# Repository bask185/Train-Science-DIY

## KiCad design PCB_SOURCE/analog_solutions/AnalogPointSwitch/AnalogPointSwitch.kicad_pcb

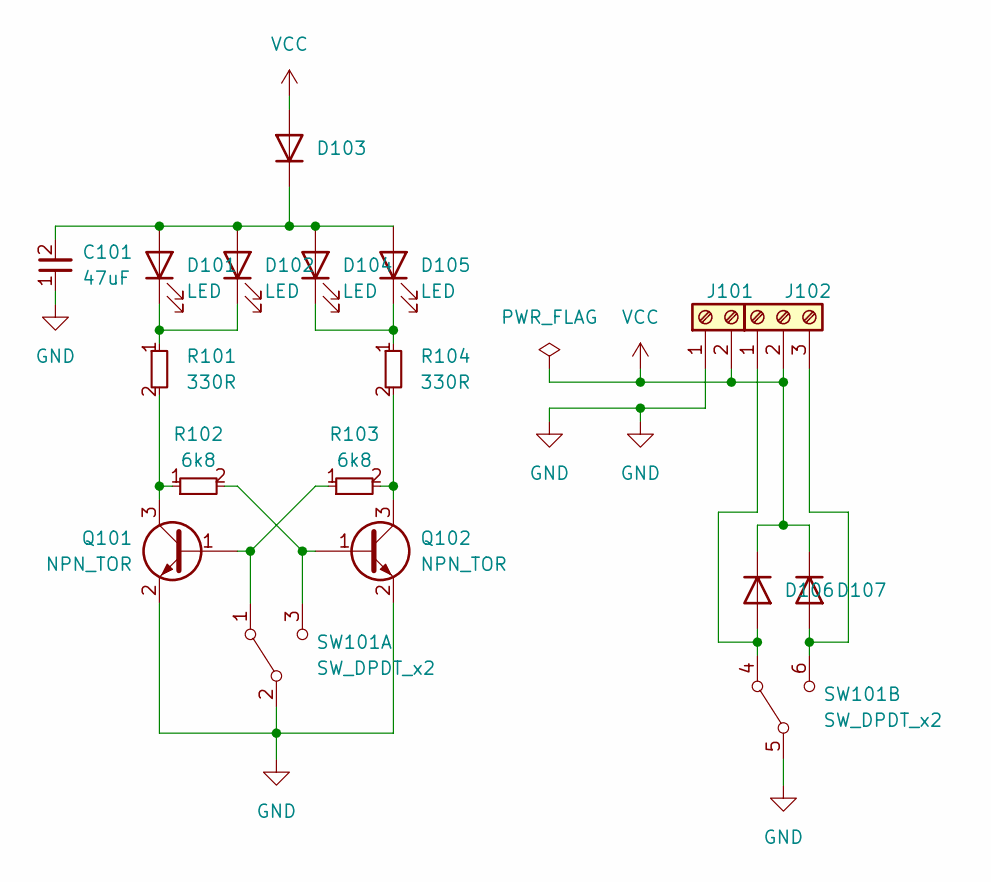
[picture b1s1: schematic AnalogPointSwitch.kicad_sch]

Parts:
C101: 47uF; C_1206_3216Metric; JLCPCB Part# C96123
D101, D102, D104, D105: LED; LED_D3.0mm
D103, D106, D107: 1N4148WS; D_SOD-323; JLCPCB Part# C2128
J101: Screw_Terminal_01x02; PhoenixContact_MCV_1,5_2-G-3.5_1x02_P3.50mm_Vertical
J102: Screw_Terminal_01x03; PhoenixContact_MCV_1,5_3-G-3.5_1x03_P3.50mm_Vertical
Q101, Q102: NPN_TOR; SOT-23; JLCPCB Part# C2145
R101, R104: 330R; R_0603_smalltext; JLCPCB Part# C23138
R102, R103: 6k8; R_0603_smalltext; JLCPCB Part# C23212
SW101: SW_DPDT_x2; MTS_DPDT

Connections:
GND: C101.1, J101.1, Q101.2 (E), Q102.2 (E), SW101.2 (B), SW101.5 (B)
unnamed: C101.2, D101.2 (A), D102.2 (A), D103.1 (K), D104.2 (A), D105.2 (A)
unnamed: D101.1 (K), D102.1 (K), R101.1
unnamed: D104.1 (K), D105.1 (K), R104.1
unnamed: D106.2 (A), J102.1, SW101.4 (A)
unnamed: D107.2 (A), J102.3, SW101.6 (C)
unnamed: Q101.1 (B), R103.1, SW101.1 (A)
unnamed: Q101.3 (C), R101.2, R102.1
unnamed: Q102.1 (B), R102.2, SW101.3 (C)
unnamed: Q102.3 (C), R103.2, R104.2
VCC: D103.2 (A), D106.1 (K), D107.1 (K), J101.2, J102.2

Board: 2 copper layers, 17 parts (5 on the bottom side), 11 nets, no tracks yet.

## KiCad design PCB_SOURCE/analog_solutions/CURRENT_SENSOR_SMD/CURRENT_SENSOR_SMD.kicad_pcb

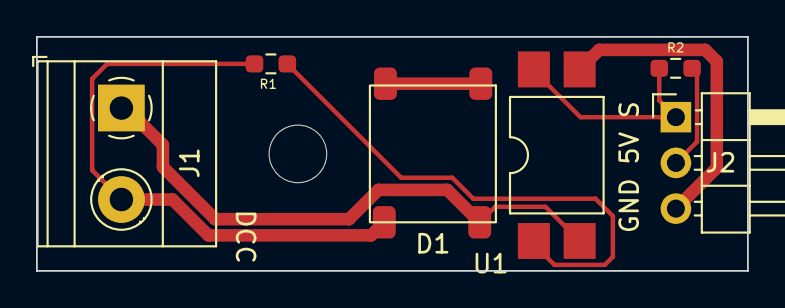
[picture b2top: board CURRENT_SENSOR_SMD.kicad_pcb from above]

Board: 2 copper layers, 39.5 x 13.0 mm, 6 parts (0 on the bottom side), 7 nets.

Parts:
D1: 4A rectifier
J1: Screw_Terminal_01x02; TerminalBlock_Phoenix_MKDS-1,5-2-5.08_1x02_P5.08mm_Horizont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
J2: Conn_01x03_Pin; PinHeader_1x03_P2.54mm_Horizontal
R1: 47R; R_0603_smalltext
R2: 10k; R_0603_smalltext
U1: EL814; SMDIP-4_W9.53mm

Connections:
+5V: J2.2, R2.2
GND: J2.3, U1.3
unnamed: D1.1 (+), D1.2 (-)
unnamed: D1.4, J1.1, U1.2
unnamed: D1.3, J1.2, R1.2
unnamed: J2.1, R2.1, U1.4
unnamed: R1.1, U1.1

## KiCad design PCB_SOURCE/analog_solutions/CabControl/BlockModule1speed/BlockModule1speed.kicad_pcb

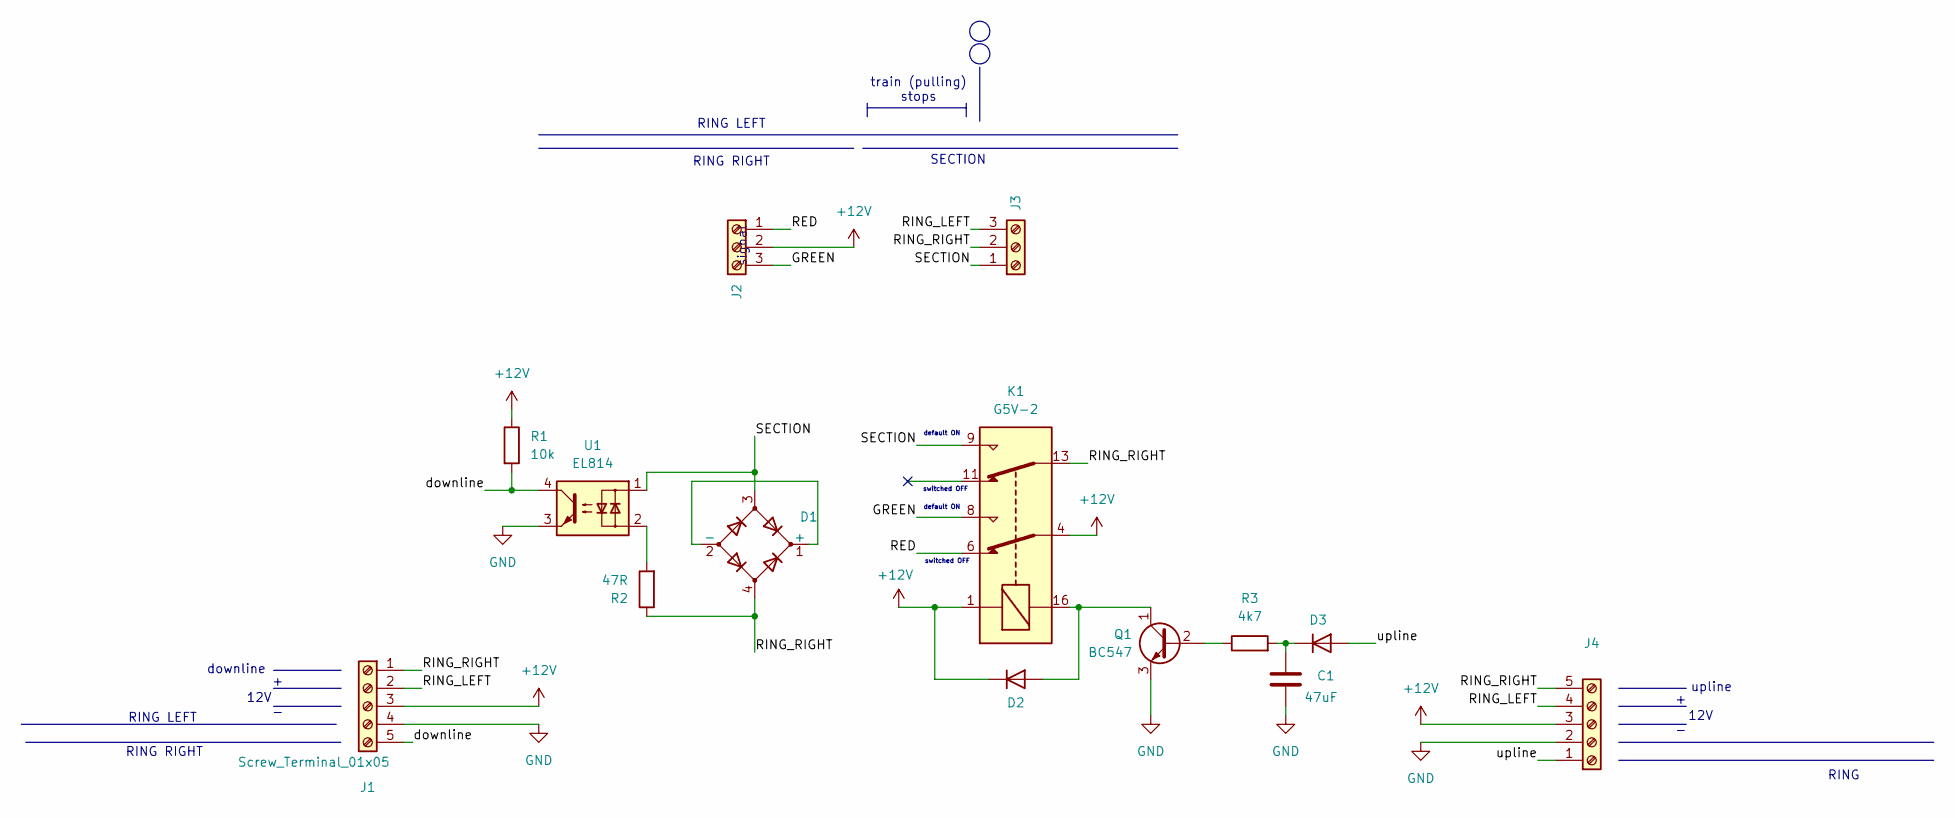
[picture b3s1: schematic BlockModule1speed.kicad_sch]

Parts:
C1: 47uF; C_Disc_D3.0mm_W2.0mm_P2.50mm
D1: D_Bridge_+-AA; Diode_Bridge_Round_D9.0mm
D2, D3: D; D_DO-34_SOD68_P7.62mm_Horizontal
J1, J4: Screw_Terminal_01x05; PhoenixContact_MC_1,5_5-G-3.5_1x05_P3.50mm_Horizontal
J2, J3: Screw_Terminal_01x03; PhoenixContact_MC_1,5_3-G-3.5_1x03_P3.50mm_Horizontal
K1: G5V-2; Relay_DPDT_Omron_G5V-2
Q1: BC547; TO-92_Inline_Wide
R1: 10k; R_Axial_DIN0204_L3.6mm_D1.6mm_P7.62mm_Horizontal
R2: 47R; R_Axial_DIN0204_L3.6mm_D1.6mm_P7.62mm_Horizontal
R3: 4k7; R_Axial_DIN0204_L3.6mm_D1.6mm_P7.62mm_Horizontal
U1: EL814; DIP-4_W7.62mm

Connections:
+12V: D2.1 (K), J1.3, J2.2, J4.3, K1.1, K1.4, R1.1
/GREEN: J2.3, K1.8
/RED: J2.1, K1.6
/RING_LEFT: J1.2, J3.3, J4.4
/RING_RIGHT: D1.4, J1.1, J3.2, J4.5, K1.13, R2.1
/SECTION: D1.3, J3.1, K1.9, U1.1
/downline: J1.5, R1.2, U1.4
/upline: D3.2 (A), J4.1
GND: C1.2, J1.4, J4.2, Q1.3 (E), U1.3
unnamed: D1.1 (+), D1.2 (-)
unnamed: D2.2 (A), K1.16, Q1.1 (C)
unnamed: C1.1, D3.1 (K), R3.2
unnamed: Q1.2 (B), R3.1
unnamed: R2.2, U1.2

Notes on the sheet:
downline
12V
RING
upline
train (pulling) stops
RING RIGHT
default ON
switched OFF
SECTION
RING LEFT
signal

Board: 2 copper layers, 14 parts (0 on the bottom side), 14 nets, no tracks yet.

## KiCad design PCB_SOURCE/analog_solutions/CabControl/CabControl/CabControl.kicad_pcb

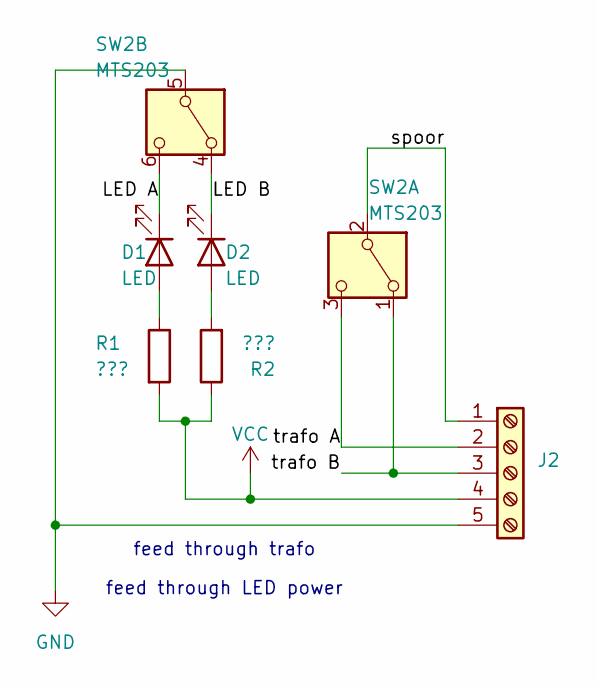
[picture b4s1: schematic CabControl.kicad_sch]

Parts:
D1, D2: LED; LED_D3.0mm
J2: Screw_Terminal_01x05; PhoenixContact_MCV_1,5_5-G-3.5_1x05_P3.50mm_Vertical
R1, R2: ???; R_Axial_DIN0204_L3.6mm_D1.6mm_P7.62mm_Horizontal
SW2: MTS203; MTS_DPDT

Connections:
/LED A: D1.1 (K), SW2.6 (C)
/LED B: D2.1 (K), SW2.4 (A)
/spoor: J2.1, SW2.2 (B)
/trafo A: J2.2, SW2.3 (C)
/trafo B: J2.3, SW2.1 (A)
GND: J2.5, SW2.5 (B)
unnamed: D1.2 (A), R1.1
unnamed: D2.2 (A), R2.2
VCC: J2.4, R1.2, R2.1

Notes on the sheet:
feed through LED power
feed through trafo

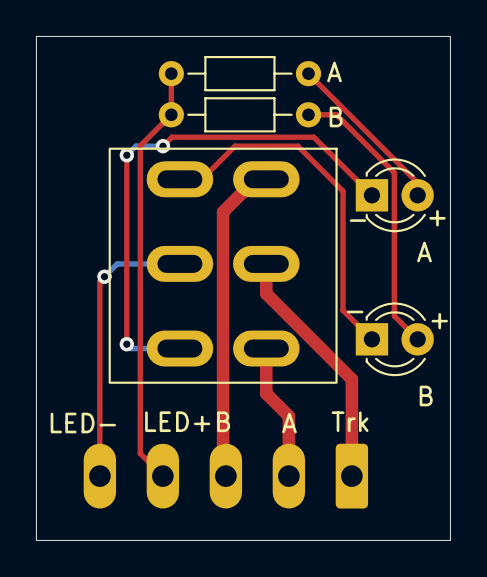
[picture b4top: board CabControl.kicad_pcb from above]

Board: 2 copper layers, 23.0 x 28.0 mm, 6 parts (1 on the bottom side), 9 nets.

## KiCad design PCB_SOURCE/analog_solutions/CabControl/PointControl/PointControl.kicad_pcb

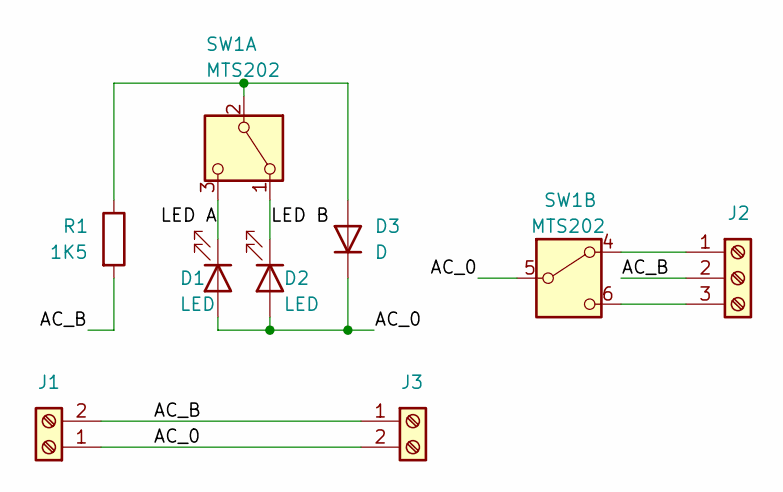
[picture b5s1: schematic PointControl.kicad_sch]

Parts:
D1, D2: LED; LED_D3.0mm
D3: D; D_DO-34_SOD68_P7.62mm_Horizontal
J1, J3: Screw_Terminal_01x02; PhoenixContact_MC_1,5_2-G-3.5_1x02_P3.50mm_Horizontal
J2: Screw_Terminal_01x03; PhoenixContact_MC_1,5_3-G-3.5_1x03_P3.50mm_Horizontal
R1: 1K5; R_Axial_DIN0204_L3.6mm_D1.6mm_P7.62mm_Horizontal
SW1: MTS202; MTS_DPDT

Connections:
/AC_0: D1.2 (A), D2.2 (A), D3.1 (K), J1.1, J3.2, SW1.5 (B)
/AC_B: J1.2, J2.2, J3.1, R1.2
/LED A: D1.1 (K), SW1.3 (C)
/LED B: D2.1 (K), SW1.1 (A)
unnamed: D3.2 (A), R1.1, SW1.2 (B)
unnamed: J2.1, SW1.4 (A)
unnamed: J2.3, SW1.6 (C)

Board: 2 copper layers, 8 parts (3 on the bottom side), 7 nets, no tracks yet.

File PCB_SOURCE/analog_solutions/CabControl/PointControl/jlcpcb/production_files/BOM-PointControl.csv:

Comment,Designator,Footprint,LCSC
1K5,R1,R_Axial_DIN0204_L3.6mm_D1.6mm_P7.62mm_Horizontal,
Screw_Terminal_01x03,J2,"PhoenixContact_MC_1,5_3-G-3.5_1x03_P3.50mm_Horizontal",
Screw_Terminal_01x02,J1,"PhoenixContact_MC_1,5_2-G-3.5_1x02_P3.50mm_Horizontal",
LED,D1,LED_D3.0mm,
LED,D2,LED_D3.0mm,
MTS202,SW1,MTS_DPDT,
D,D3,D_DO-34_SOD68_P7.62mm_Horizontal,
Screw_Terminal_01x02,J3,"PhoenixContact_MC_1,5_2-G-3.5_1x02_P3.50mm_Horizontal",

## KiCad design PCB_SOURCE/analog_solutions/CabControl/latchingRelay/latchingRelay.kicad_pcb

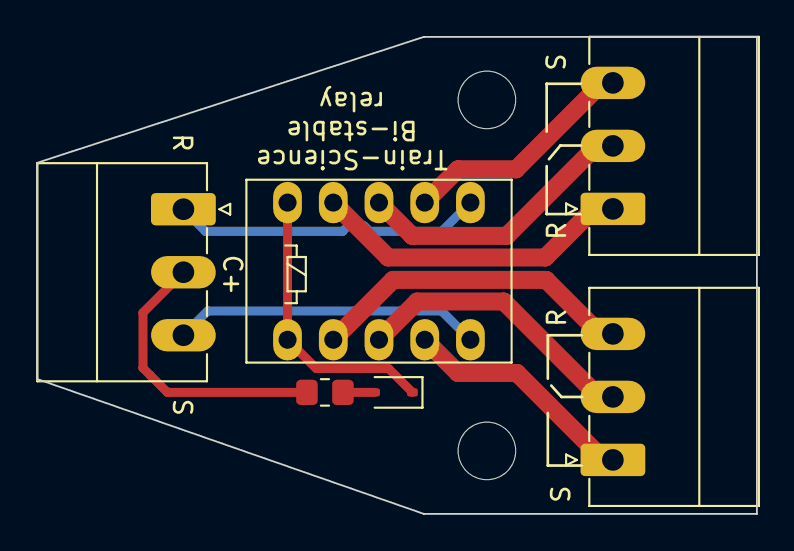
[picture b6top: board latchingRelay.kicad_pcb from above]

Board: 2 copper layers, 40.0 x 26.5 mm, 6 parts (0 on the bottom side), 11 nets.

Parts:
D101: 1N4148WS; D_SOD-323
J101, J102, J103: Screw_Terminal_01x03; PhoenixContact_MC_1,5_3-G-3.5_1x03_P3.50mm_Horizontal
K101: AZ850P2-x; Relay_DPDT_FRT5
R101: 47R; R_0805_handsolder-smalltext

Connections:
unnamed: D101.2 (A), R101.1
unnamed: D101.1 (K), K101.1, K101.10
unnamed: J101.1, K101.6
unnamed: J101.2, R101.2
unnamed: J101.3, K101.5
unnamed: J102.1, K101.4
unnamed: J102.2, K101.3
unnamed: J102.3, K101.2
unnamed: J103.1, K101.9
unnamed: J103.2, K101.8
unnamed: J103.3, K101.7

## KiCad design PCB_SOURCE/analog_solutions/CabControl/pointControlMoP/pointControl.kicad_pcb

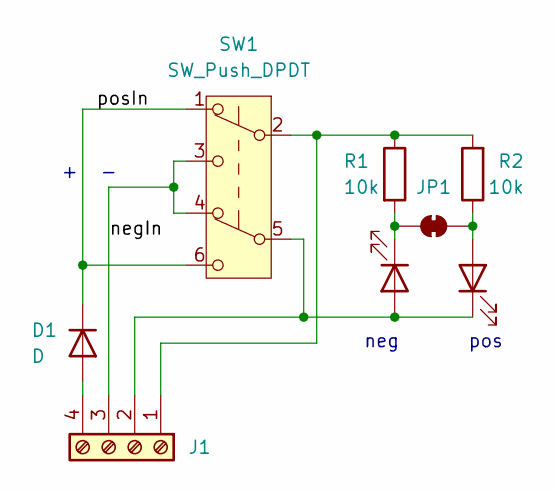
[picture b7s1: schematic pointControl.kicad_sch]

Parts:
D1: D; D_DO-34_SOD68_P7.62mm_Horizontal
D_NEG2: LED; LED_D3.0mm
D_POS3: D; LED_D3.0mm
J1: Screw_Terminal_01x04; PhoenixContact_MCV_1,5_4-G-3.5_1x04_P3.50mm_Vertical
JP1: SolderJumper_2_Bridged; SolderJumper-2_P1.3mm_Bridged_RoundedPad1.0x1.5mm
R1, R2: 10k; R_Axial_DIN0204_L3.6mm_D1.6mm_P7.62mm_Horizontal
SW1: SW_Push_DPDT; MTS_DPDT

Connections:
/negIn: J1.3, SW1.3 (C), SW1.4 (A)
/posIn: D1.1 (K), SW1.1 (A), SW1.6 (C)
unnamed: D1.2 (A), J1.4
unnamed: D_NEG2.2 (A), D_POS3.1 (K), J1.2, SW1.5 (B)
unnamed: D_NEG2.1 (K), JP1.1 (A), R1.2
unnamed: D_POS3.2 (A), JP1.2 (B), R2.1
unnamed: J1.1, R1.1, R2.2, SW1.2 (B)

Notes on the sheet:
pos
neg

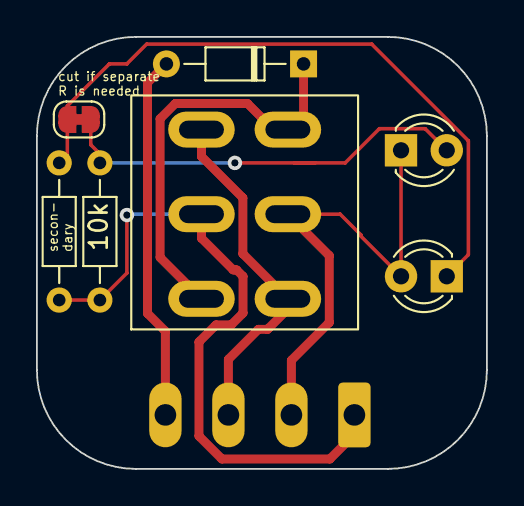
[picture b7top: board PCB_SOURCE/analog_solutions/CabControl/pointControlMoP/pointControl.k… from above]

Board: 2 copper layers, 25.0 x 24.0 mm, 8 parts (1 on the bottom side), 7 nets.

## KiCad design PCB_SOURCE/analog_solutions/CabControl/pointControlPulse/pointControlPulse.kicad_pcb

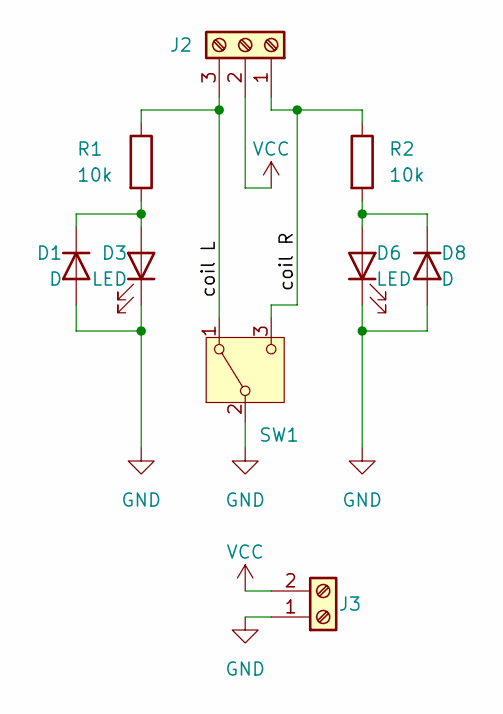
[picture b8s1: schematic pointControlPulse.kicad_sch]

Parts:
D1, D8: D; D_DO-34_SOD68_P7.62mm_Horizontal
D3, D6: LED; LED_D3.0mm
J2: Screw_Terminal_01x03; PhoenixContact_MCV_1,5_3-G-3.5_1x03_P3.50mm_Vertical
J3: Screw_Terminal_01x02; PhoenixContact_MCV_1,5_2-G-3.5_1x02_P3.50mm_Vertical
R1, R2: 10k; R_Axial_DIN0204_L3.6mm_D1.6mm_P7.62mm_Horizontal
SW1: SW_SPDT; SW_Toggle_Blue_wSlots

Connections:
/coil L: J2.3, R1.1, SW1.1 (A)
/coil R: J2.1, R2.1, SW1.3 (C)
GND: D1.2 (A), D3.1 (K), D6.1 (K), D8.2 (A), J3.1, SW1.2 (B)
unnamed: D1.1 (K), D3.2 (A), R1.2
unnamed: D6.2 (A), D8.1 (K), R2.2
VCC: J2.2, J3.2

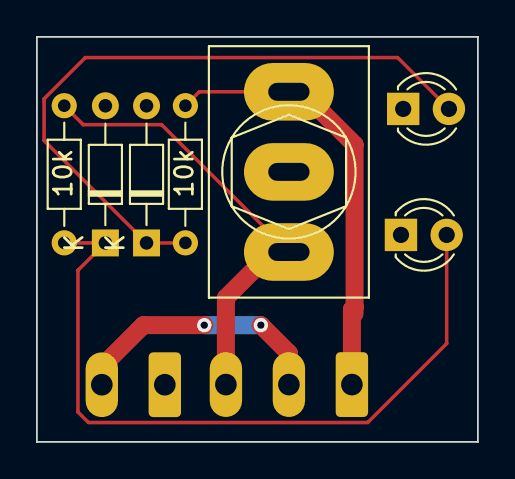
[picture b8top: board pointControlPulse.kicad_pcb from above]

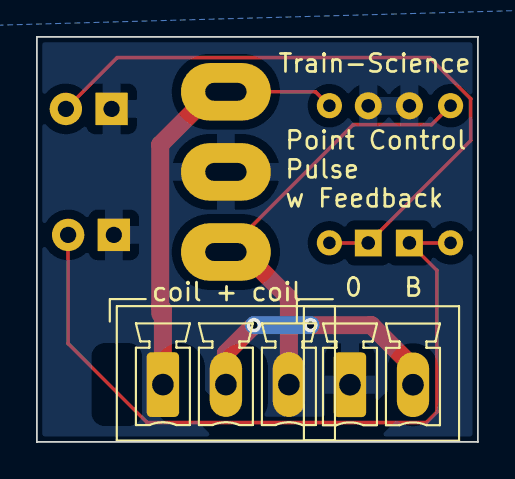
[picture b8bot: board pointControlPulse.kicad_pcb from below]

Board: 2 copper layers, 24.5 x 22.5 mm, 9 parts (2 on the bottom side), 6 nets.

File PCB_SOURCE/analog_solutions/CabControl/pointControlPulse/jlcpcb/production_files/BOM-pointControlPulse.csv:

Comment,Designator,Footprint,LCSC
D,D8,D_DO-34_SOD68_P7.62mm_Horizontal,
D,D1,D_DO-34_SOD68_P7.62mm_Horizontal,
LED,D3,LED_D3.0mm,
SW_SPDT,SW1,SW_Toggle_Blue_wSlots,
LED,D6,LED_D3.0mm,
10k,R2,R_Axial_DIN0204_L3.6mm_D1.6mm_P7.62mm_Horizontal,
10k,R1,R_Axial_DIN0204_L3.6mm_D1.6mm_P7.62mm_Horizontal,
Screw_Terminal_01x02,J3,"PhoenixContact_MCV_1,5_2-G-3.5_1x02_P3.50mm_Vertical",
Screw_Terminal_01x03,J2,"PhoenixContact_MCV_1,5_3-G-3.5_1x03_P3.50mm_Vertical",
